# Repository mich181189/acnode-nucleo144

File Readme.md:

ACNode Nucleo-144 Overlay
=========

# What Is This?
This is an **unfinished** design for an addon board to fit a Nucleo-144, turning it into an ACNode.

# Why?
The current ACNode hardware and software (https://github.com/londonhackspace/acnode-cl) is based around a TI Connected Launchpad. These no doubt looked cool when they were new, but there haven't been any new revisions for some time. On top of this, the current code is based around Energia, an Arduino port for TI Connected Launchpads.

Nowadays, there are other inexpensive development boards available with Ethernet. ST make a large range of Nucleo-144 boards for various microcontrollers. They're more capable, and seem to have better software support.

The software could really do with a rewrite anyway, so there isn't much lost there. It should be possible to make software that builds for both TI Connected Launchpads and ST Nucleo boards (Early-ish work based on FreeRTOS here: https://github.com/mich181189/acnode-cl)

# Features
* Connects to a Nucleo-144 board
* Provides connections to both existing 8P8C readers and the new (still in development, though coming along nicely) RS-422 connected serial readers
* 7-12V input with reverse polarity protection
* SPI Flash for configuration and card caching
* On-board LED mirroring reader LED
* Isolated Tool On input (should accept 3.3-12V)
* Relay for turning on tools, opening doors e.t.c

# Changes from Existing ACNode Boards

* SPI Flash instead of SDCard
I don't think we've ever actually fitted the SD Card. The STM32 MCUs don't have built-in EEPROMs, and we need somewhere to store configuration. Putting these two observations together, it makes sense to fit some SPI storage (EEPROM or Flash) for storage. EEPROMs are easier to write small amounts to, but are smaller. Flash has a lower write cycle count, however tend to be larger, and with a wear levelling filesystem, should be fine.

* On-board LED
When an ACNode is mounted to the other side of a door to its reader, it can be difficult to see the state of the reader since the LED is on the other side of a door. The obvious solution to this is to also put an LED on the ACNode.

* On-board Button
Similar to the on-board LED, this mirrors the functionality of the button on the reader, for easier maintainence

* Isolated tool on pin
Tools can be noisy. By isolating the tool on signal using an optoisolator, we can reduce coupling between the tool and the ACNode.

* Provides RS-422 reader connection
Since we want to be able to use the new reader boards, we need a way to conect them.

* 7-12V input with reverse polarity protection
Not exactly a new requirement, but the Nucleo-144 boards have regulators built in with 7-12V input range, so we may as well add this as an option. Reverse polarity protection because it makes sense to have! A previous board does have a reverse-biased diode for polarity "protection" but it's probably more of a smoke signal.

# Nucleo-144 Boards
Nucleo-144 boards do vary a bit. This board is intended to work with the following boards (which have basically the same pin usage), however will probably work with many other Nucleo-144 boards:

| Board | Features | Example Price | Example Source |
| ----- | -------- | ------------- | -------------- |
| NUCLEO-H743ZI2 | Arm Cortex M7 with 2MB Flash, 1MB RAM, L1 Cache, running at up to 480MHz | £26.21 | [https://uk.rs-online.com/web/p/microcontroller-development-tools/1939787/](RS 193-9787) |
| NUCLEO-F767ZI | Arm Cortex M7 with 2MB Flash, 512KB RAM, L1 Cache, running at up to 216MHz | £22.38 | [https://uk.rs-online.com/web/p/microcontroller-development-tools/1231052/](RS 123-1052) |
| NUCLEO-F756ZG | Arm Cortex M7 with 1MB Flash, 320KB RAM, L1 Cache, HW Crypto, running at up to 216MHz | £22.31 | [https://uk.rs-online.com/web/p/microcontroller-development-tools/1750680/](RS 175-0680) |

# TODO
* Exit Button Support
* A jumper on the ISL3176 ~RE line would allow a single	board to support 5V and 12V readers
* Footprints for 3.81mm	connectors are too tight - holes too small

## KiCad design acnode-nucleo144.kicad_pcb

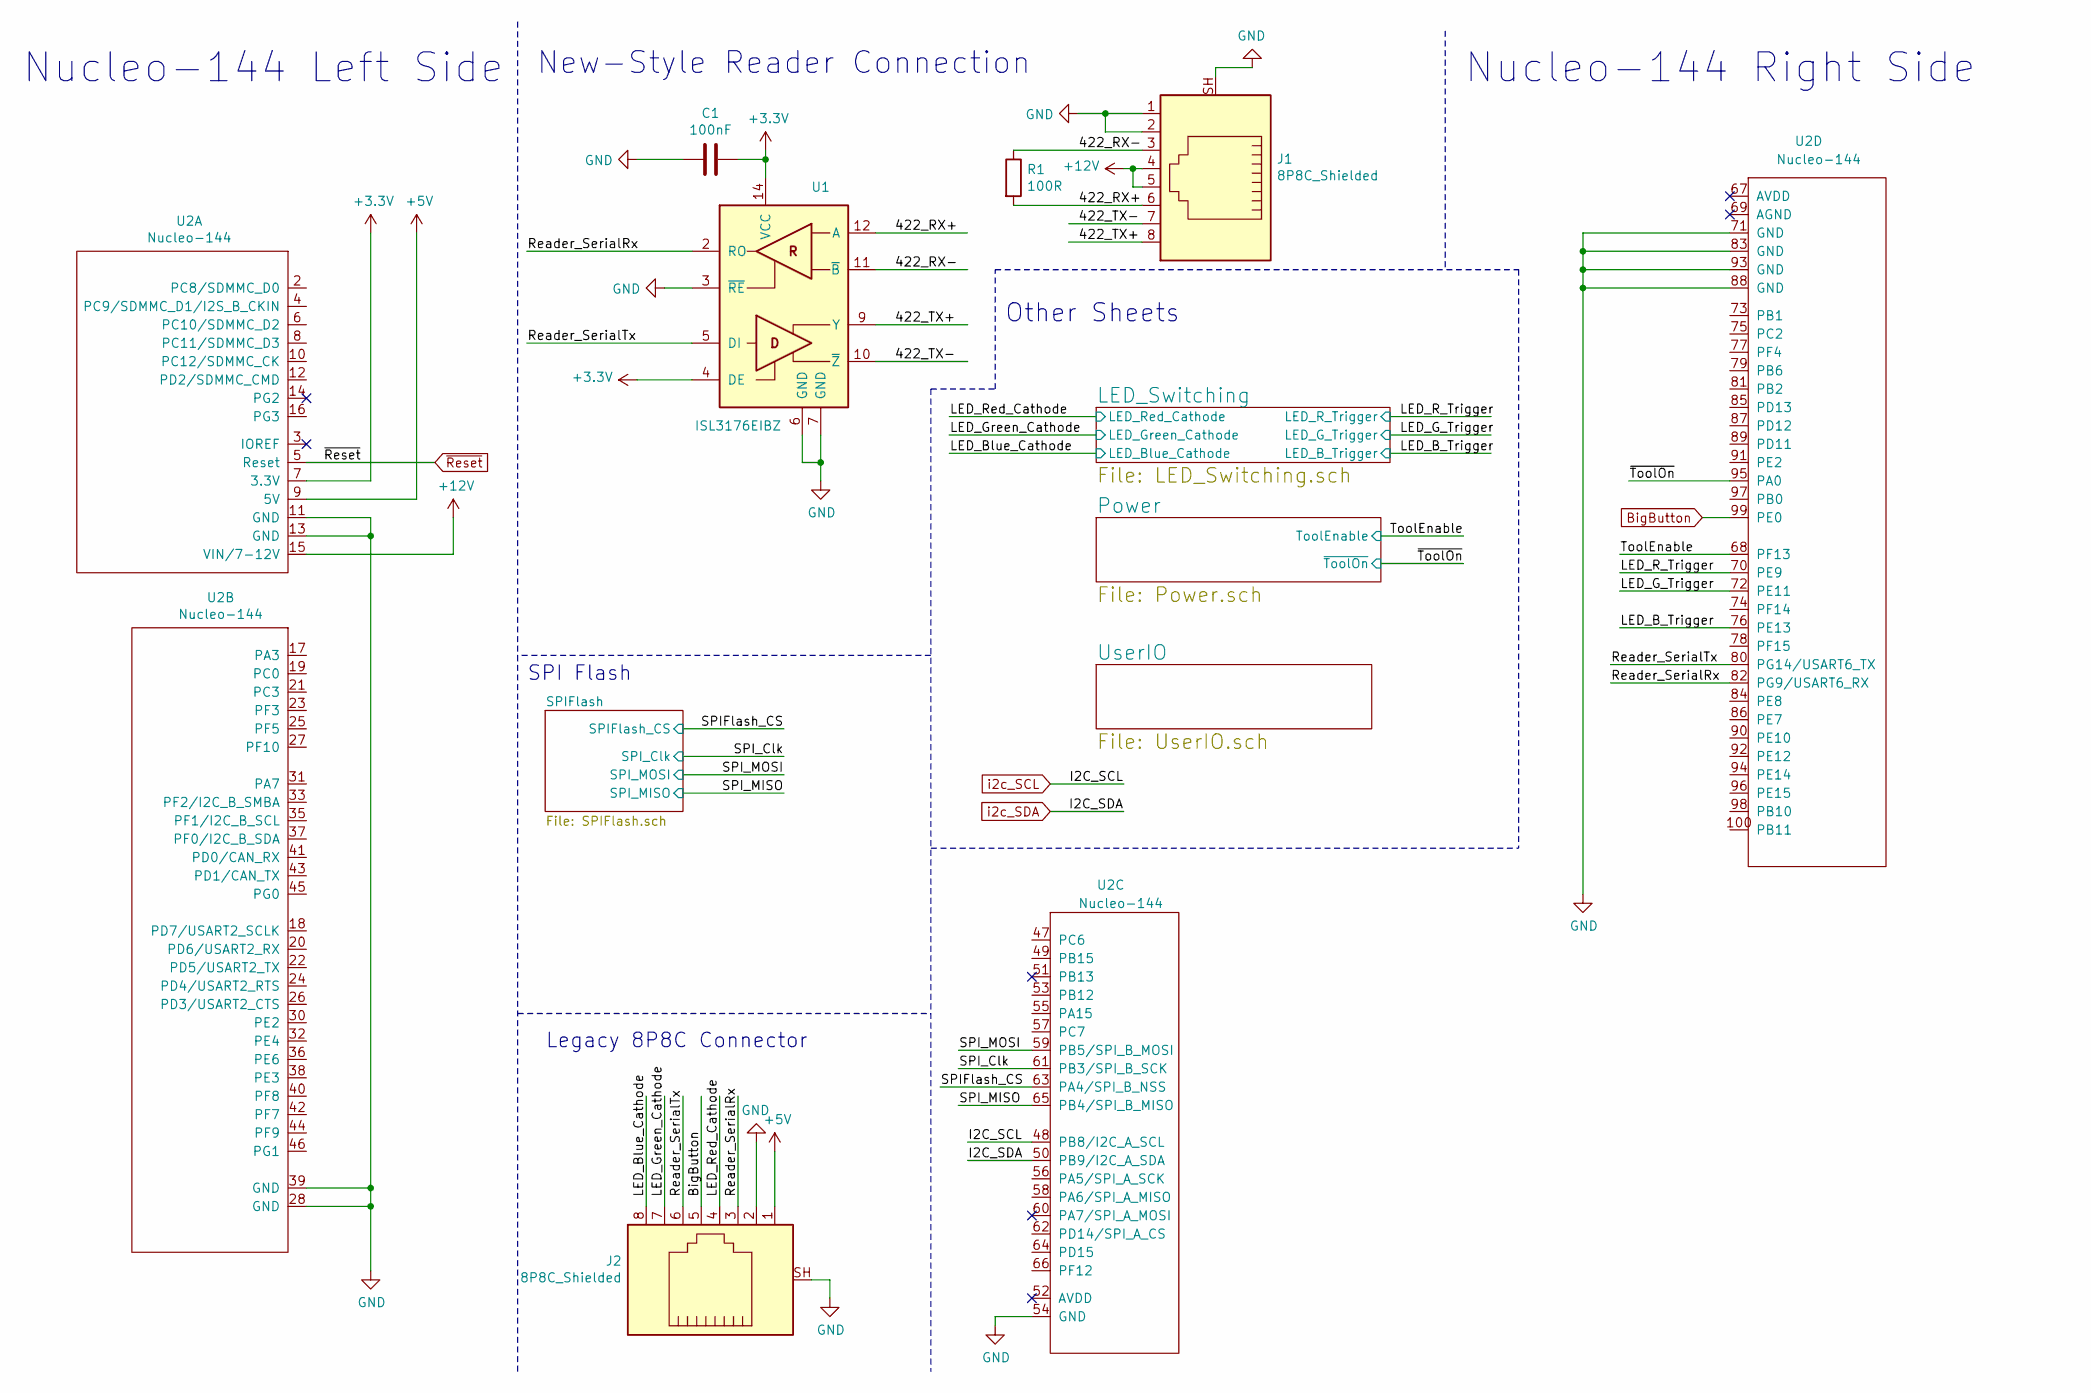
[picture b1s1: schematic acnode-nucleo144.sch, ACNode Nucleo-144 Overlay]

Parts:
C1: 100nF; C_0603_1608Metric
J1, J2: 8P8C_Shielded; RJ45_Ninigi_GE
R1: 100R; R_0603_1608Metric
U1: ISL3176EIBZ; SOIC-14_3.9x8.7mm_P1.27mm
U2: Nucleo-144

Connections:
+3V3: C1.1, U1.4 (DE), U1.14 (VCC), U2.7 (3.3V); also elsewhere on the board
+5V: J2.1, U2.9 (5V); also elsewhere on the board
+12V: J1.4, J1.5, U2.15 (VIN/7-12V); also elsewhere on the board
/422_RX+: J1.6, R1.2, U1.12 (A)
/422_RX-: J1.3, R1.1, U1.11 (~B)
/422_TX+: J1.8, U1.9 (Y)
/422_TX-: J1.7, U1.10 (~Z~)
/LED_B_Trigger: U2.76 (PE13); also elsewhere on the board
/LED_Blue_Cathode: J2.8; also elsewhere on the board
/LED_G_Trigger: U2.72 (PE11); also elsewhere on the board
/LED_Green_Cathode: J2.7; also elsewhere on the board
/LED_R_Trigger: U2.70 (PE9); also elsewhere on the board
/LED_Red_Cathode: J2.4; also elsewhere on the board
/Reader_SerialRx: J2.3, U1.2 (RO), U2.82 (PG9/USART6_RX)
/Reader_SerialTx: J2.6, U1.5 (DI), U2.80 (PG14/USART6_TX)
/SPIFlash_CS: U2.63 (PA4/SPI_B_NSS); also elsewhere on the board
/SPI_Clk: U2.61 (PB3/SPI_B_SCK); also elsewhere on the board
/SPI_MISO: U2.65 (PB4/SPI_B_MISO); also elsewhere on the board
/SPI_MOSI: U2.59 (PB5/SPI_B_MOSI); also elsewhere on the board
/ToolEnable: U2.68 (PF13); also elsewhere on the board
/~ToolOn: U2.95 (PA0); also elsewhere on the board
BigButton: J2.5, U2.99 (PE0); also elsewhere on the board
GND: C1.2, J1.1, J1.2, J1.SH, J2.2, J2.SH, U1.3 (~RE), U1.6 (GND), U1.7 (GND), U2.11 (GND), U2.13 (GND), U2.28 (GND), U2.39 (GND), U2.54 (GND), U2.71 (GND), U2.83 (GND), U2.88 (GND), U2.93 (GND); also elsewhere on the board
i2c_SCL: U2.48 (PB8/I2C_A_SCL); also elsewhere on the board
i2c_SDA: U2.50 (PB9/I2C_A_SDA); also elsewhere on the board
~Reset: U2.5 (Reset); also elsewhere on the board

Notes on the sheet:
Nucleo-144 Left Side
Nucleo-144 Right Side
Legacy 8P8C Connector
SPI Flash
New-Style Reader Connection
Other Sheets

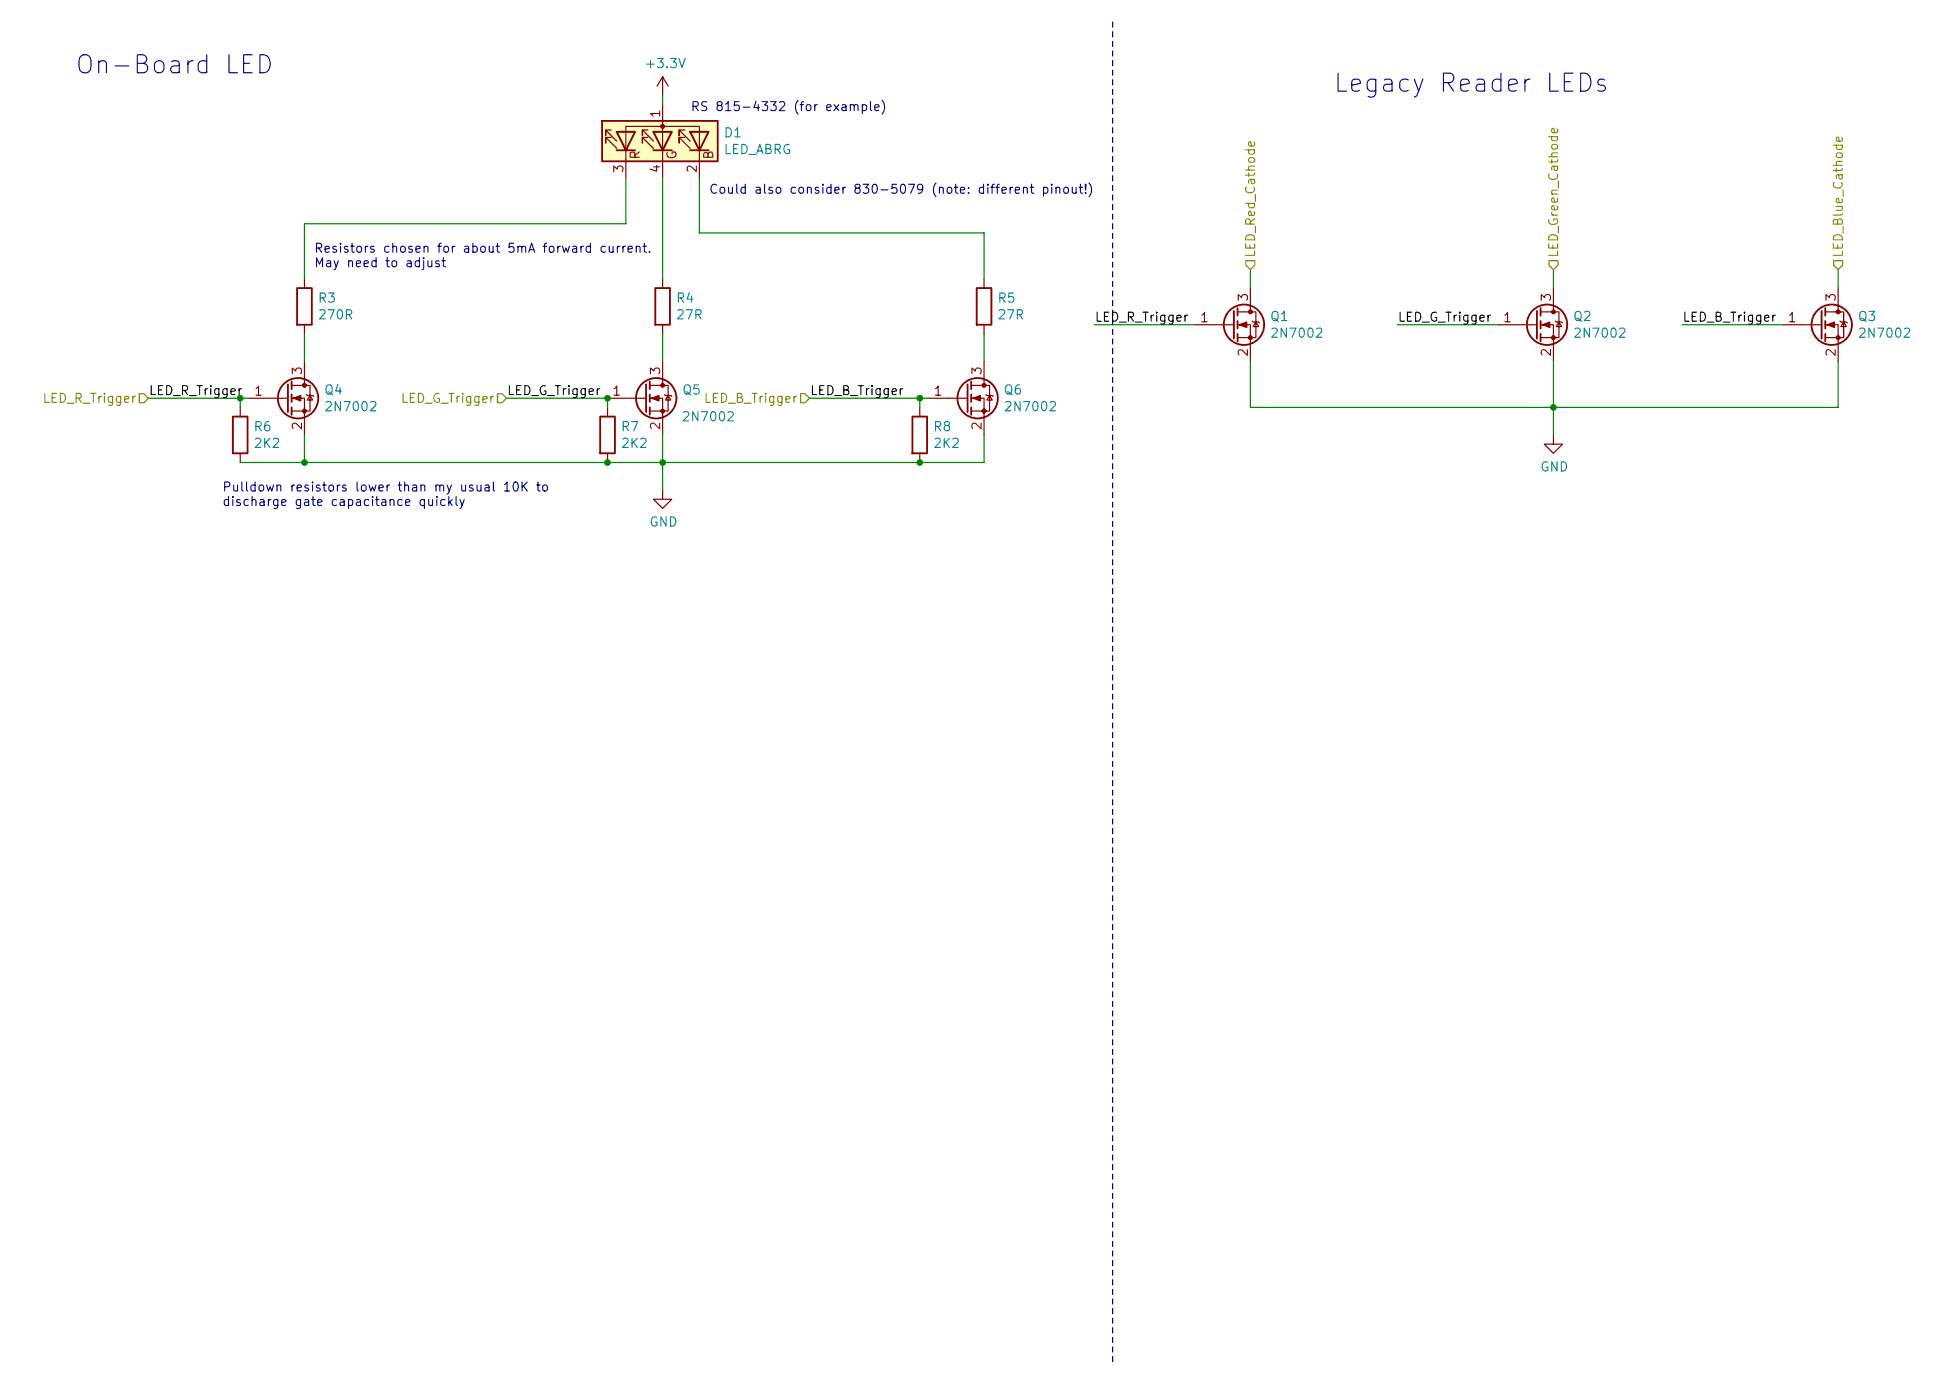
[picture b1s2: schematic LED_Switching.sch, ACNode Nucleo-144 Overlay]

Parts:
D1: LED_ABRG; Wurth_3528_LED
Q1, Q2, Q3, Q4, Q5, Q6: 2N7002; SOT-23
R3: 270R; R_0603_1608Metric
R4, R5: 27R; R_0603_1608Metric
R6, R7, R8: 2K2; R_0603_1608Metric

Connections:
+3V3: D1.1 (A); also elsewhere on the board
/LED_B_Trigger: Q3.1 (G), Q6.1 (G), R8.1; also elsewhere on the board
/LED_Blue_Cathode: Q3.3 (D); also elsewhere on the board
/LED_G_Trigger: Q2.1 (G), Q5.1 (G), R7.1; also elsewhere on the board
/LED_Green_Cathode: Q2.3 (D); also elsewhere on the board
/LED_R_Trigger: Q1.1 (G), Q4.1 (G), R6.1; also elsewhere on the board
/LED_Red_Cathode: Q1.3 (D); also elsewhere on the board
GND: Q1.2 (S), Q2.2 (S), Q3.2 (S), Q4.2 (S), Q5.2 (S), Q6.2 (S), R6.2, R7.2, R8.2; also elsewhere on the board
unnamed: D1.2 (BK), R5.1
unnamed: D1.3 (RK), R3.1
unnamed: D1.4 (GK), R4.1
unnamed: Q4.3 (D), R3.2
unnamed: Q5.3 (D), R4.2
unnamed: Q6.3 (D), R5.2

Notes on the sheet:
RS 815-4332 (for example)
On-Board LED
Legacy Reader LEDs
Pulldown resistors lower than my usual 10K to discharge gate capacitance quickly
Could also consider 830-5079 (note: different pinout!)
Resistors chosen for about 5mA forward current. May need to adjust

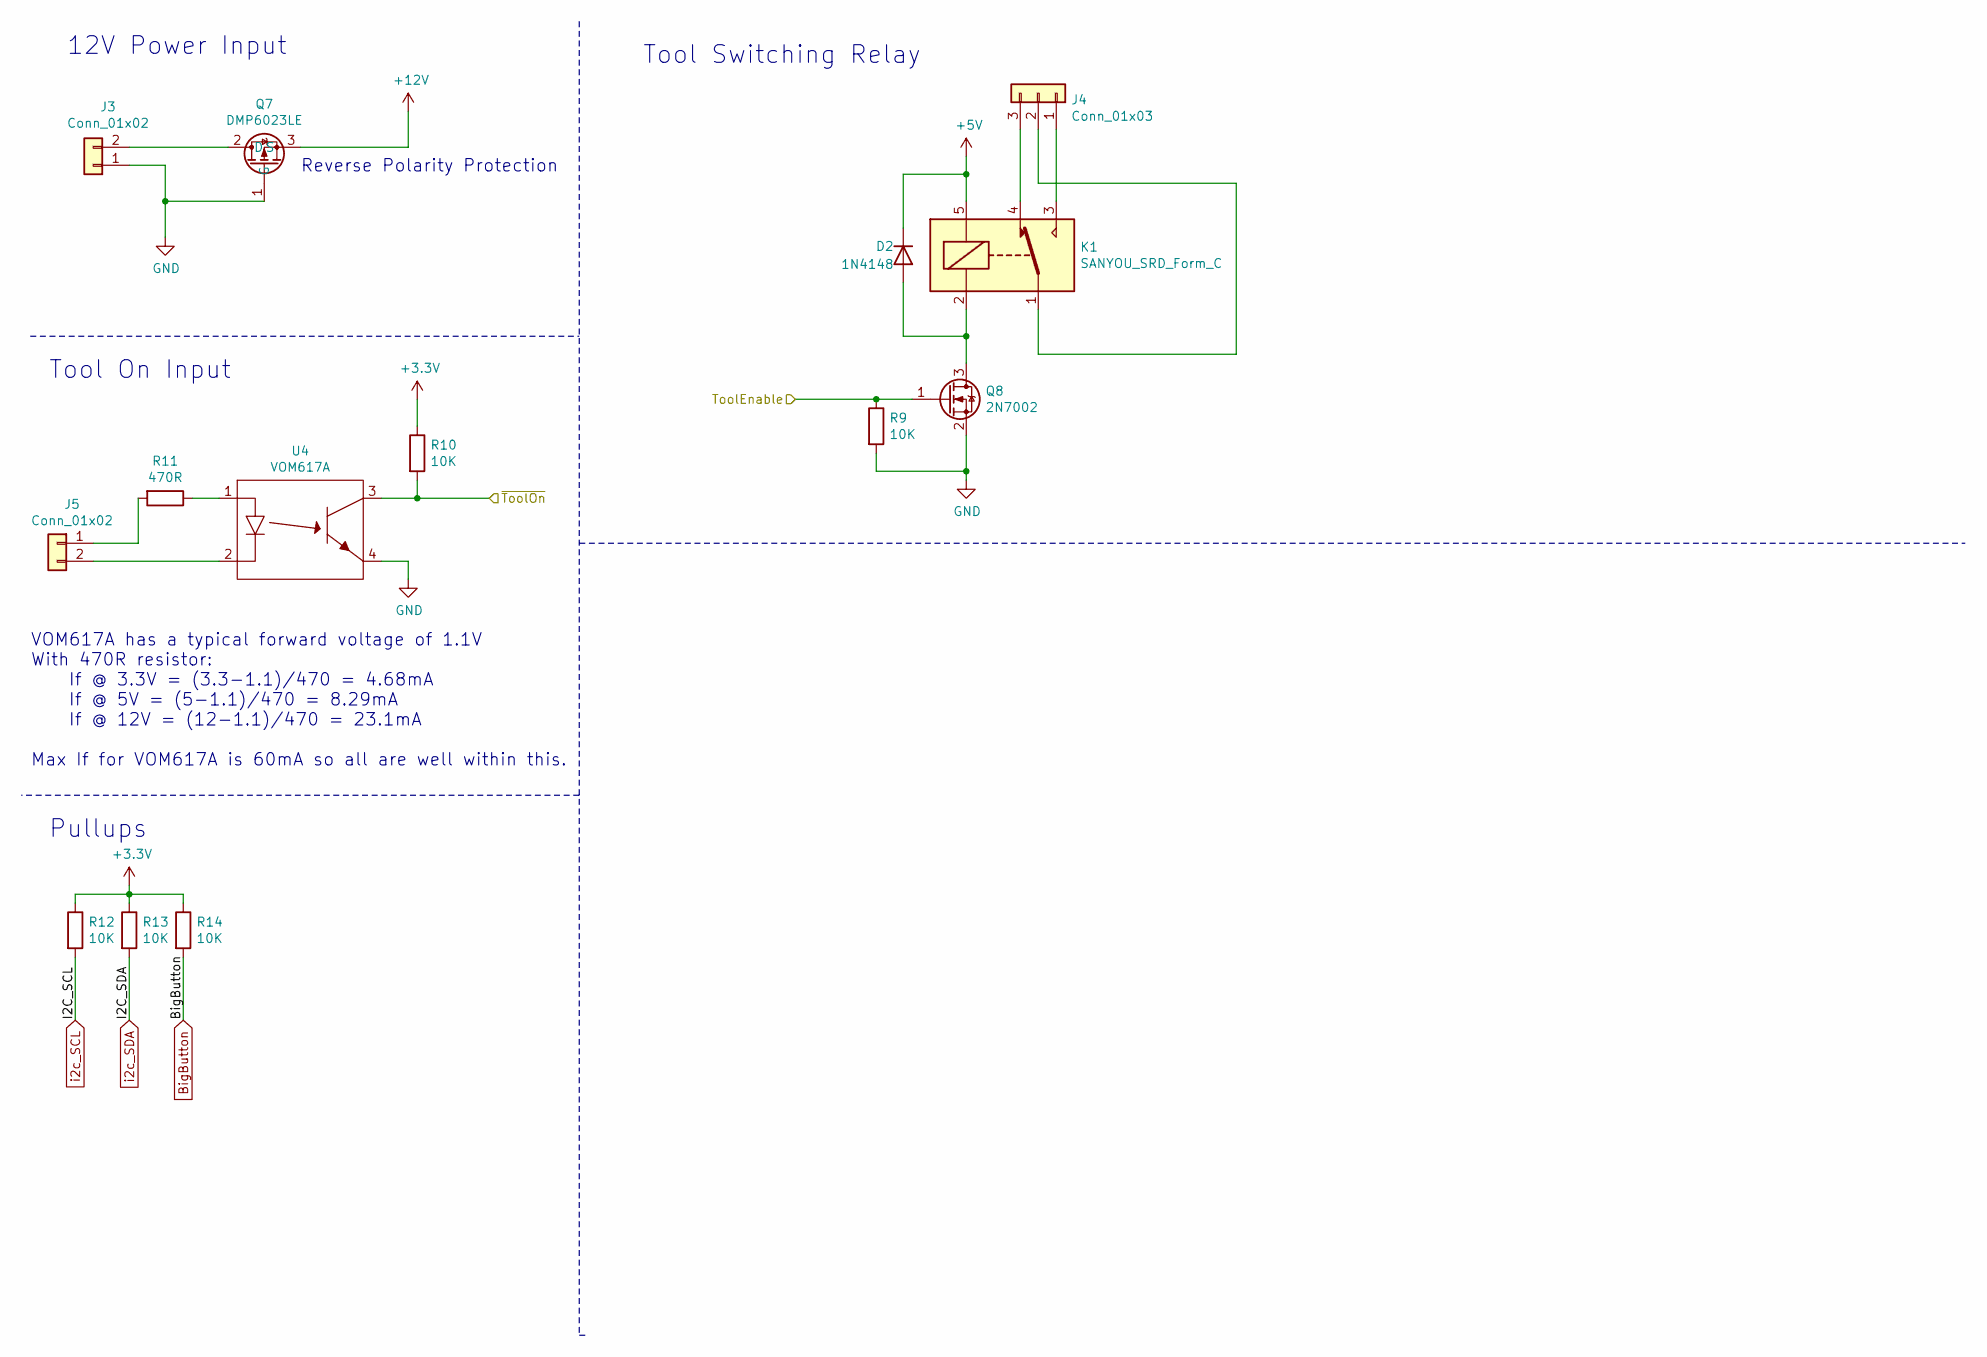
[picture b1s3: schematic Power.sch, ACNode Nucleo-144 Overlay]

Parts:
D2: 1N4148; D_DO-35_SOD27_P7.62mm_Horizontal
J3: Conn_01x02; Connector-5.08mm
J4: Conn_01x03; Connector-3.81mm-3pin
J5: Conn_01x02; Connector-3.81mm-2pin
K1: SANYOU_SRD_Form_C; Relay_SPDT_SANYOU_SRD_Series_Form_C
Q7: DMP6023LE; SOT-223
Q8: 2N7002; SOT-23
R9, R10, R12, R13, R14: 10K; R_0603_1608Metric
R11: 470R; R_0603_1608Metric
U4: VOM617A; VOM617A-4SOP

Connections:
+3V3: R10.1, R12.1, R13.1, R14.1; also elsewhere on the board
+5V: D2.1 (K), K1.5; also elsewhere on the board
+12V: Q7.3 (S); also elsewhere on the board
/ToolEnable: Q8.1 (G), R9.1; also elsewhere on the board
/~ToolOn: R10.2, U4.3; also elsewhere on the board
BigButton: R14.2; also elsewhere on the board
GND: J3.1, Q7.1 (G), Q8.2 (S), R9.2, U4.4; also elsewhere on the board
unnamed: D2.2 (A), K1.2, Q8.3 (D)
unnamed: J3.2, Q7.2 (D), Q7.4 (Tab)
unnamed: J4.1, K1.3
unnamed: J4.2, K1.1
unnamed: J4.3, K1.4
unnamed: J5.1, R11.2
unnamed: J5.2, U4.2
unnamed: R11.1, U4.1
i2c_SCL: R12.2; also elsewhere on the board
i2c_SDA: R13.2; also elsewhere on the board

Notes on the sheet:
Reverse Polarity Protection
12V Power Input
Tool Switching Relay
Tool On Input
VOM617A has a typical forward voltage of 1.1V With 470R resistor: If @ 3.3V = (3.3-1.1)/470 = 4.68mA If @ 5V = (5-1.1)/470 = 8.29mA If @ 12V = (12-1.1)/470 = 23.1mA Max If for VOM617A is 60mA so all are well within this.
Pullups

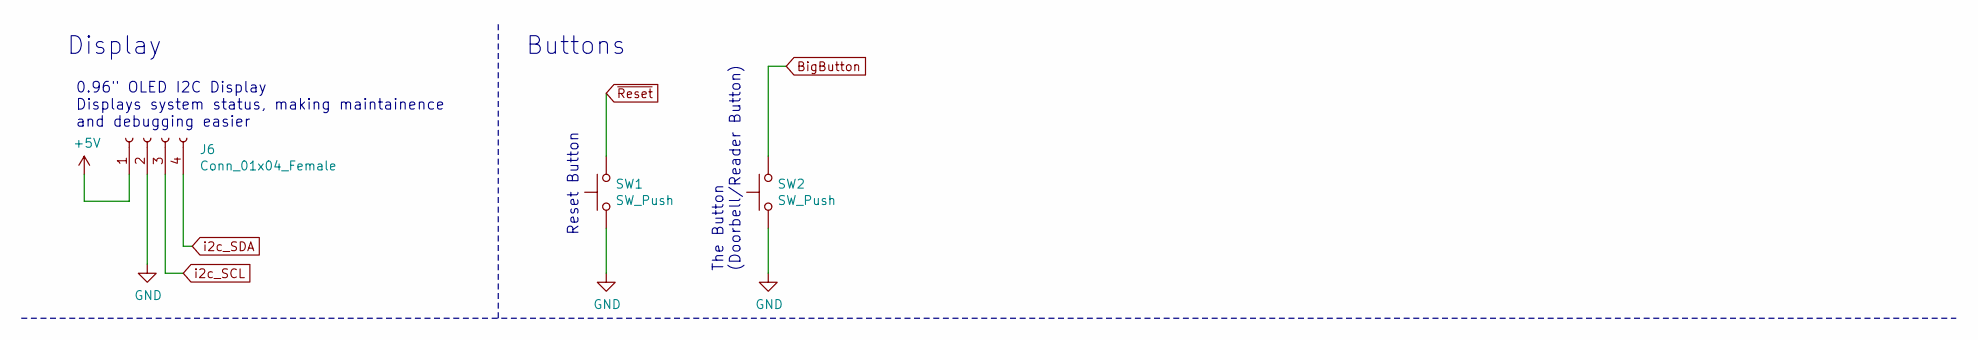
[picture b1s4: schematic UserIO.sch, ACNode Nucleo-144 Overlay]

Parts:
J6: Conn_01x04_Female; PinHeader_1x04_P2.54mm_Vertical
SW1, SW2: SW_Push; SW_PUSH_6mm

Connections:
+5V: J6.1; also elsewhere on the board
BigButton: SW2.2; also elsewhere on the board
GND: J6.2, SW1.1, SW2.1; also elsewhere on the board
i2c_SCL: J6.3; also elsewhere on the board
i2c_SDA: J6.4; also elsewhere on the board
~Reset: SW1.2; also elsewhere on the board

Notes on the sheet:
Display
0.96" OLED I2C Display Displays system status, making maintainence and debugging easier
Buttons
Reset Button
The Button (Doorbell/Reader Button)

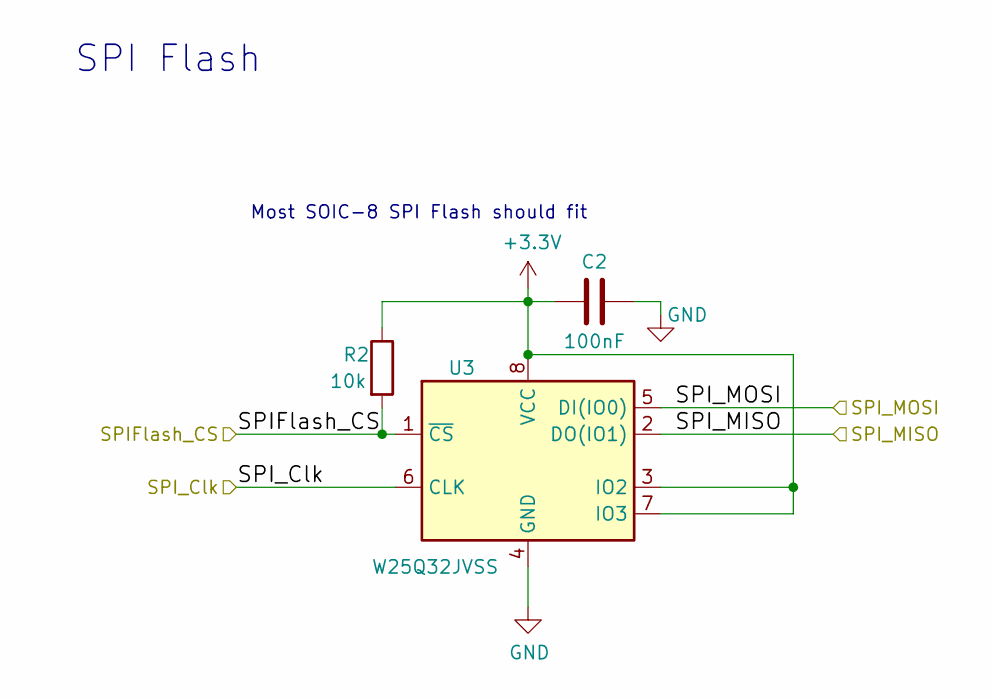
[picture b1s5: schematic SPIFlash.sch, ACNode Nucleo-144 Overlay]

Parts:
C2: 100nF; C_0603_1608Metric
R2: 10k; R_0603_1608Metric
U3: W25Q32JVSS; SOIC-8_5.23x5.23mm_P1.27mm

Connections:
+3V3: C2.2, R2.1, U3.3 (IO2), U3.7 (IO3), U3.8 (VCC); also elsewhere on the board
/SPIFlash_CS: R2.2, U3.1 (~CS); also elsewhere on the board
/SPI_Clk: U3.6 (CLK); also elsewhere on the board
/SPI_MISO: U3.2 (DO(IO1)); also elsewhere on the board
/SPI_MOSI: U3.5 (DI(IO0)); also elsewhere on the board
GND: C2.1, U3.4 (GND); also elsewhere on the board

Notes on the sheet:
Most SOIC-8 SPI Flash should fit
SPI Flash

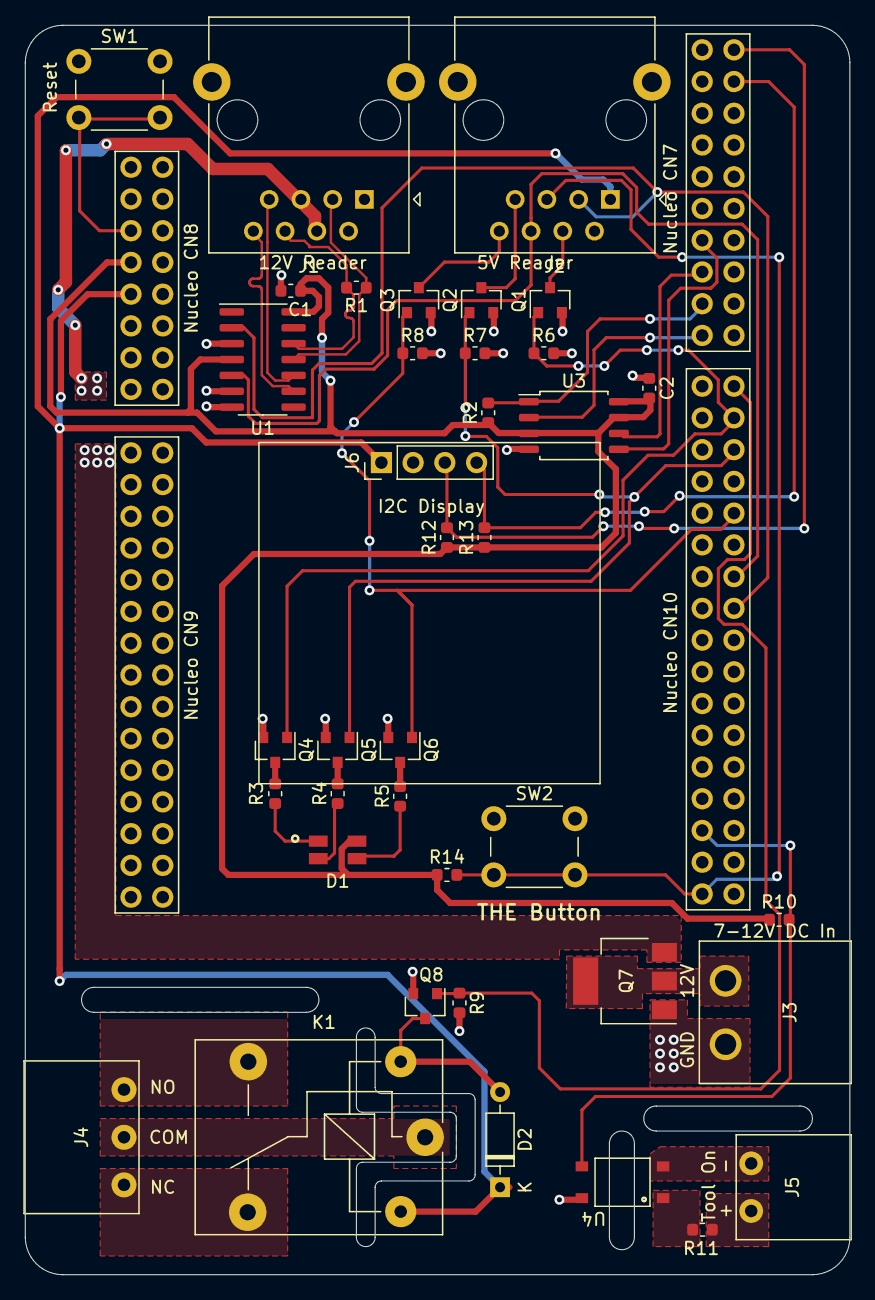
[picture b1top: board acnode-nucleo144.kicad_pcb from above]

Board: 2 copper layers, 66.0 x 100.0 mm, 39 parts (0 on the bottom side), 40 nets.

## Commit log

2020-11-28 Initial commit of draft
2020-11-28 Annotated some symbols and linked nets properly between sheets
2020-11-28 Updated PDF and a few schematic tweaks
2020-11-29 First pass at routing board fully
    Also fixed a stupid error on the Nucleo-144 footprint
2020-11-29 Switched to shielded 8P8C jack
2020-11-30 Added TODO to reademe
2020-12-18 Some changes I found on my computer
2020-12-18 Updated PDF
2021-02-23 I built one. Still obviously needs proper software support to fully test, but it doesn't look bad
2021-02-27 Added a couple of assembly notes
